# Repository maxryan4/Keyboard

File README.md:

# Keyboard
Media Controller Keyboard using STM32F072C8

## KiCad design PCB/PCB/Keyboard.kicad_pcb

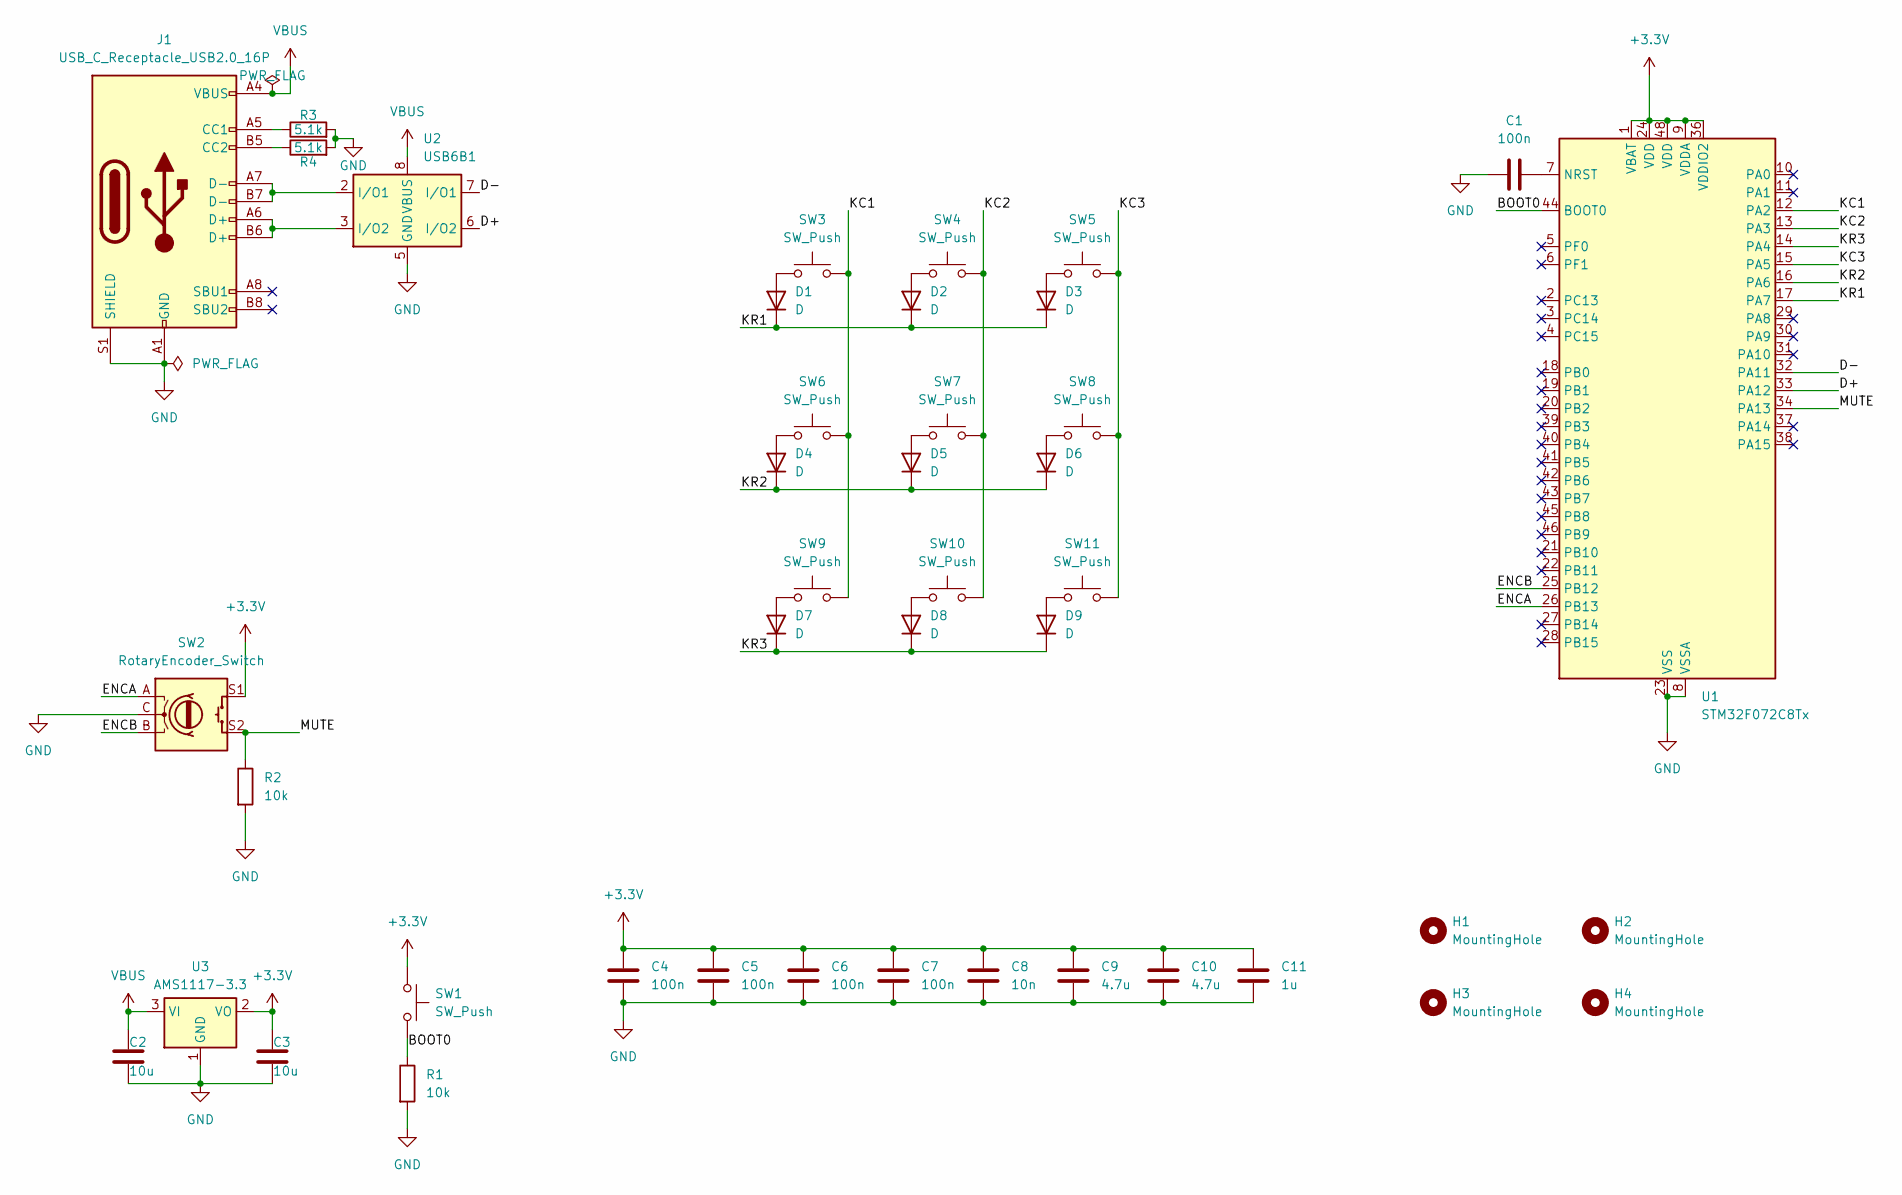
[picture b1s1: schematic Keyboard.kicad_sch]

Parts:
C1, C4, C5, C6, C7: 100n; C_0805_2012Metric
C2, C3: 10u; C_0805_2012Metric
C8: 10n; C_0805_2012Metric
C9, C10: 4.7u; C_0805_2012Metric
C11: 1u; C_0805_2012Metric
D1, D2, D3, D4, D5, D6, D7, D8, D9: D; D_0805_2012Metric
H1, H2, H3, H4: MountingHole; MountingHole_3.2mm_M3
J1: USB_C_Receptacle_USB2.0_16P; USB_C_Receptacle_GCT_USB4105-xx-A_16P_TopMnt_Horizontal
R1, R2: 10k; R_0805_2012Metric
R3, R4: 5.1k; R_0805_2012Metric
SW1: SW_Push; SW_SPST_B3S-1100
SW2: RotaryEncoder_Switch; RotaryEncoder_Alps_EC11E-Switch_Vertical_H20mm
SW3, SW4, SW5, SW6, SW7, SW8, SW9, SW10, SW11: SW_Push; SW_Hotswap_Kailh_MX_1.00u
U1: STM32F072C8Tx; LQFP-48_7x7mm_P0.5mm
U2: USB6B1; SOIC-8_3.9x4.9mm_P1.27mm
U3: AMS1117-3.3; SOT-223-3_TabPin2

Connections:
+3.3V: C3.1, C4.1, C5.1, C6.1, C7.1, C8.1, C9.1, C10.1, C11.1, SW1.1, SW2.S1, U1.1 (VBAT), U1.9 (VDDA), U1.24 (VDD), U1.36 (VDDIO2), U1.48 (VDD), U3.2 (VO)
/BOOT0: R1.1, SW1.2, U1.44 (BOOT0)
/D+: U1.33 (PA12), U2.6 (I/O2)
/D-: U1.32 (PA11), U2.7 (I/O1)
/ENCA: SW2.A, U1.26 (PB13)
/ENCB: SW2.B, U1.25 (PB12)
/KC1: SW3.2, SW6.2, SW9.2, U1.12 (PA2)
/KC2: SW4.2, SW7.2, SW10.2, U1.13 (PA3)
/KC3: SW5.2, SW8.2, SW11.2, U1.15 (PA5)
/KR1: D1.1 (K), D2.1 (K), D3.1 (K), U1.17 (PA7)
/KR2: D4.1 (K), D5.1 (K), D6.1 (K), U1.16 (PA6)
/KR3: D7.1 (K), D8.1 (K), D9.1 (K), U1.14 (PA4)
/MUTE: R2.1, SW2.S2, U1.34 (PA13)
GND: C1.1, C2.2, C3.2, C4.2, C5.2, C6.2, C7.2, C8.2, C9.2, C10.2, C11.2, J1.A1 (GND), J1.A12 (GND), J1.B1 (GND), J1.B12 (GND), J1.S1 (SHIELD), R1.2, R2.2, R3.2, R4.2, SW2.C, U1.8 (VSSA), U1.23 (VSS), U1.35 (VSS), U1.47 (VSS), U2.4 (GND), U2.5 (GND), U3.1 (GND)
unnamed: D1.2 (A), SW3.1
unnamed: D2.2 (A), SW4.1
unnamed: D3.2 (A), SW5.1
unnamed: D4.2 (A), SW6.1
unnamed: D5.2 (A), SW7.1
unnamed: D6.2 (A), SW8.1
unnamed: D7.2 (A), SW9.1
unnamed: D8.2 (A), SW10.1
unnamed: D9.2 (A), SW11.1
unnamed: J1.A5 (CC1), R3.1
unnamed: J1.B5 (CC2), R4.1
unnamed: J1.A6 (D+), J1.B6 (D+), U2.3 (I/O2)
unnamed: J1.A7 (D-), J1.B7 (D-), U2.2 (I/O1)
unnamed: C1.2, U1.7 (NRST)
VBUS: C2.1, J1.A4 (VBUS), J1.A9 (VBUS), J1.B4 (VBUS), J1.B9 (VBUS), U2.1 (VBUS), U2.8 (VBUS), U3.3 (VI)

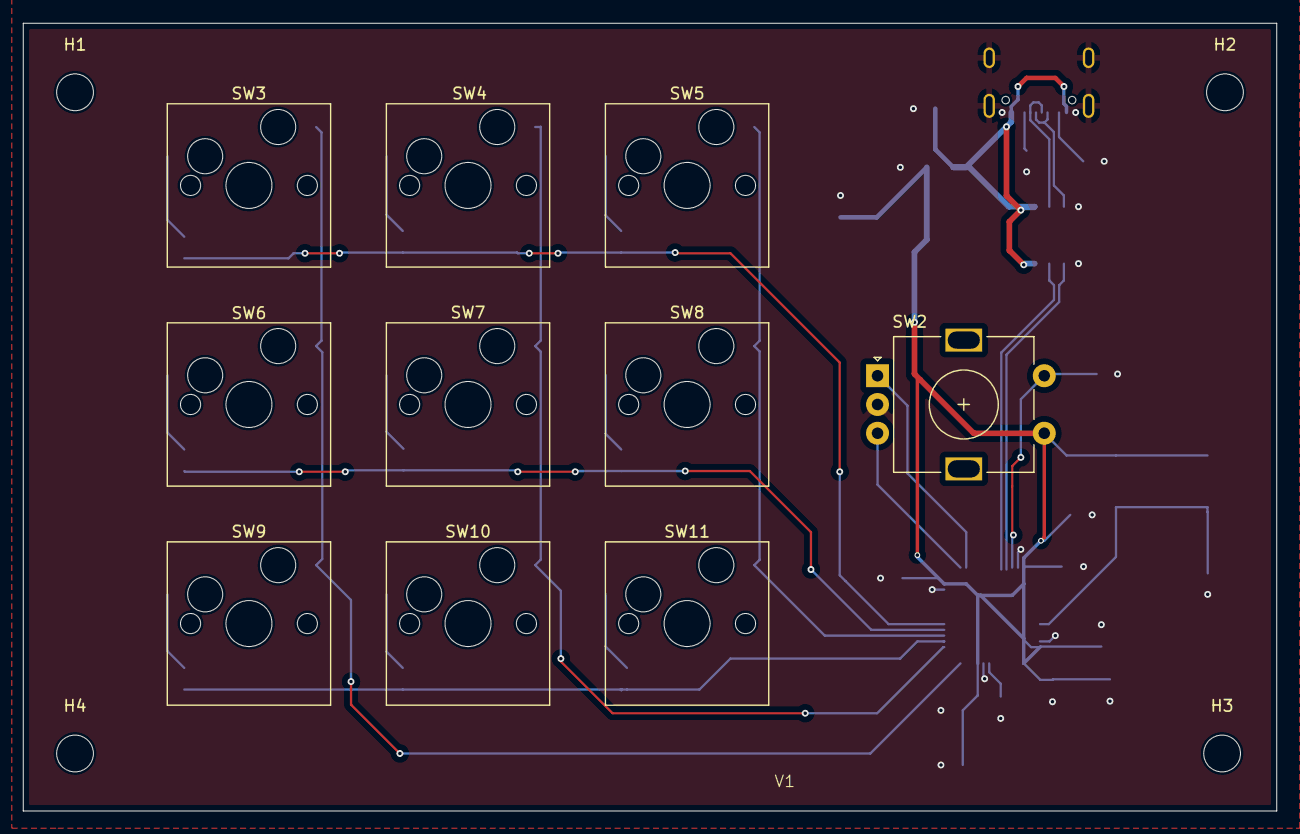
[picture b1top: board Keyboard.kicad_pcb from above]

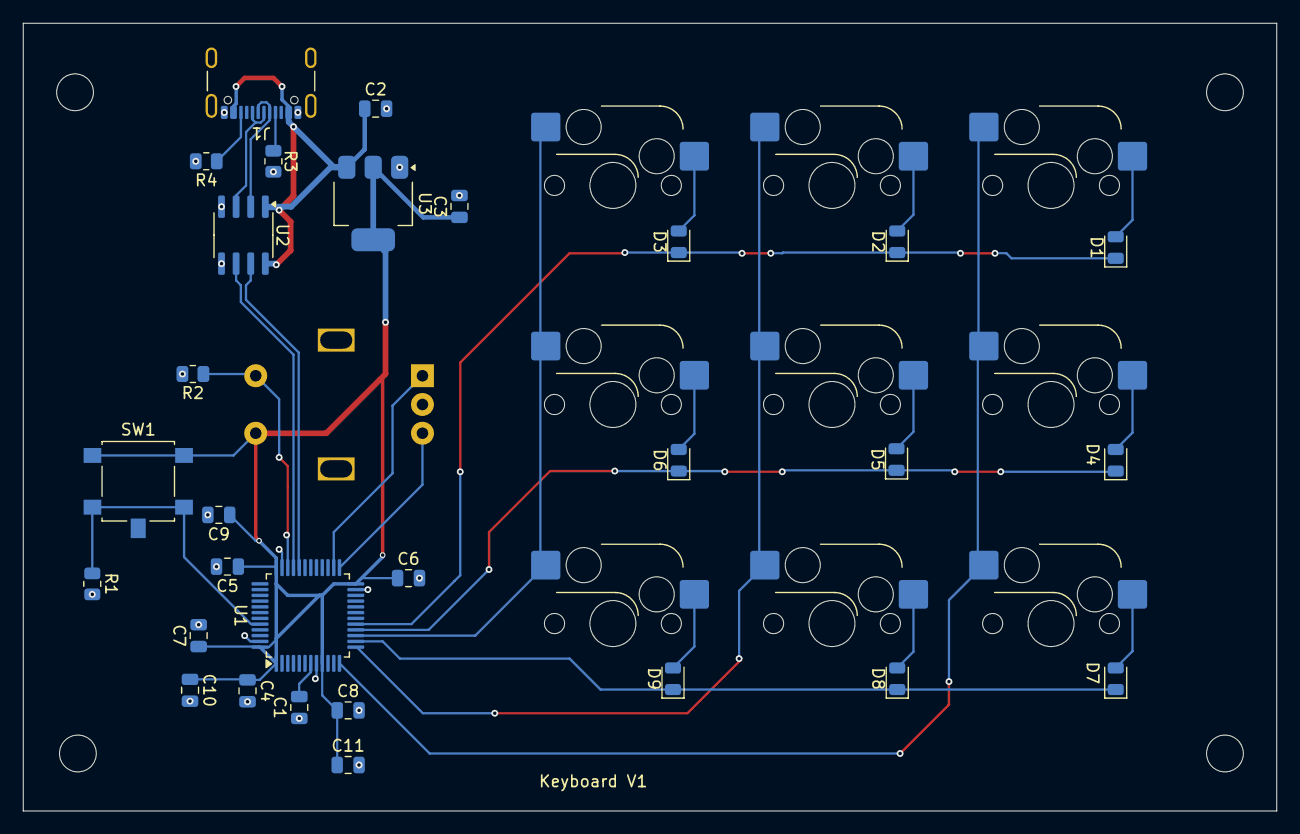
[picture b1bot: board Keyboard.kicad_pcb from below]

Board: 2 copper layers, 109.0 x 68.5 mm, 43 parts (29 on the bottom side), 29 nets.

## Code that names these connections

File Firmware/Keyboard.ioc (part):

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Mcu.Name=STM32F072C(8-B)Tx
Mcu.Package=LQFP48
Mcu.UserName=STM32F072C8Tx
PA11.Mode=Device
PA11.Signal=USB_DM
PA12.Mode=Device
PA12.Signal=USB_DP
PA13.GPIOParameters=GPIO_PuPd,GPIO_Label
PA13.GPIO_Label=MUTE
PA13.GPIO_PuPd=GPIO_PULLUP
PA13.Signal=GPIO_Input
PA2.GPIOParameters=GPIO_Label
PA2.GPIO_Label=KC1
PA2.Signal=GPIO_Output
PA3.GPIOParameters=GPIO_Label
PA3.GPIO_Label=KC2
PA3.Signal=GPIO_Output
PA4.GPIOParameters=GPIO_PuPd,GPIO_Label
PA4.GPIO_Label=KR3
PA4.GPIO_PuPd=GPIO_PULLDOWN
PA4.Signal=GPIO_Input
PA5.GPIOParameters=GPIO_Label
PA5.GPIO_Label=KC3
PA5.Signal=GPIO_Output
PA6.GPIOParameters=GPIO_PuPd,GPIO_Label
PA6.GPIO_Label=KR2
PA6.GPIO_PuPd=GPIO_PULLDOWN
PA6.Signal=GPIO_Input
PA7.GPIOParameters=GPIO_PuPd,GPIO_Label
PA7.GPIO_Label=KR1
PA7.GPIO_PuPd=GPIO_PULLDOWN
PA7.Signal=GPIO_Input
PB12.GPIOParameters=GPIO_PuPd,GPIO_Label,GPIO_ModeDefaultEXTI
PB12.GPIO_Label=ENCB
PB12.GPIO_ModeDefaultEXTI=GPIO_MODE_IT_RISING_FALLING
PB12.GPIO_PuPd=GPIO_PULLUP
PB12.Signal=GPXTI12
PB13.GPIOParameters=GPIO_PuPd,GPIO_Label,GPIO_ModeDefaultEXTI
PB13.GPIO_Label=ENCA
PB13.GPIO_ModeDefaultEXTI=GPIO_MODE_IT_RISING_FALLING
PB13.GPIO_PuPd=GPIO_PULLUP
PB13.Signal=GPXTI13
RCC.SYSCLKFreq_VALUE=48000000
RCC.SYSCLKSource=RCC_SYSCLKSOURCE_HSI48
board=custom

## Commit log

2025-07-29 PCB Design V1
2025-07-29 Minor PCB changes
2025-08-05 PCB CAD file
2025-08-19 Added basic case files
2025-08-24 Device works as an HID just outputs AB every second
2025-08-24 keyboard now have some keys implemented multimedia (consumer) keys are not implemented yet require different type of hid input
2025-08-24 Added images
2025-09-07 Added multimedia key support
    (Encoder control not implemented yet)
2025-09-07 Partially implemented encoder
2025-09-07 Updated so both encoder pins are interrupts
2025-09-13 Changes to encoder (still not working)
    The hid control works as expected just that reading from the rotary encoder still doesn't work
